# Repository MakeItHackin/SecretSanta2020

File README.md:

# SecretSanta2020
Overview of Reddit Secret Santa gift from 2020

Watch the Demo Here:
https://youtu.be/uKTaNg_Iy-Q

Review the User Guide PDF for details

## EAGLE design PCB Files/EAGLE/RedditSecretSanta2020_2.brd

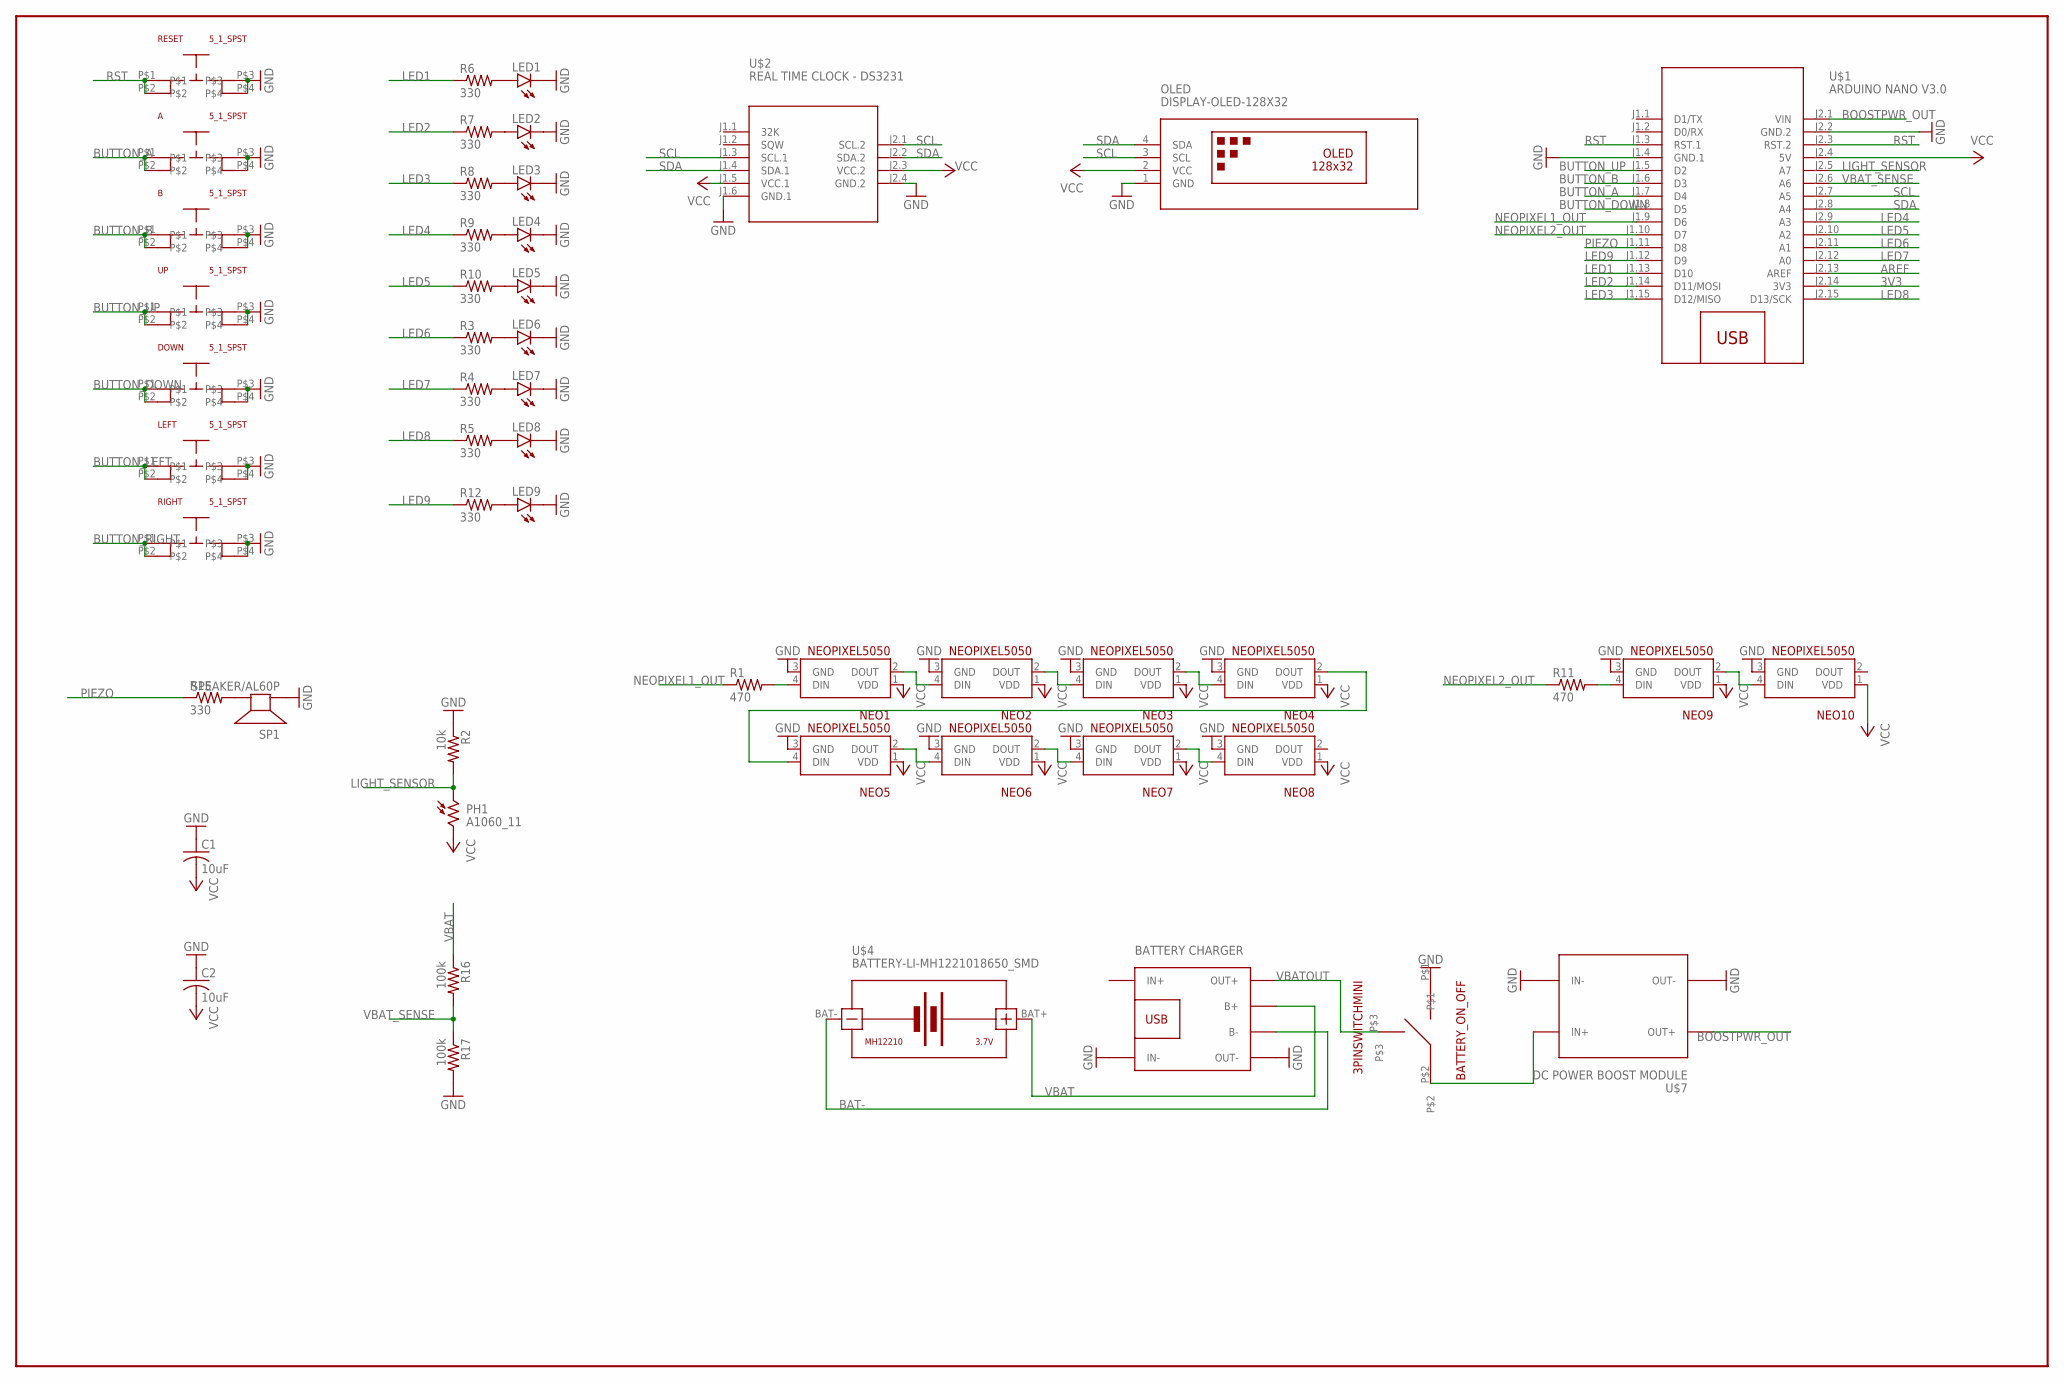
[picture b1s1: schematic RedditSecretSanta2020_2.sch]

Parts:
A: 5_1_SPST
B: 5_1_SPST
BATTERY_ON_OFF: 3PINSWITCHMINI; 3PINMINI
C1, C2: 10uF; C0805
DOWN: 5_1_SPST
LED1, LED2, LED3, LED4, LED5, LED6, LED7, LED8, LED9: LEDSML0805; SML0805
LEFT: 5_1_SPST
NEO1, NEO2, NEO3, NEO4, NEO5, NEO6, NEO7, NEO8, NEO9, NEO10: NEOPIXEL5050
OLED: DISPLAY-OLED-128X32
PH1: A1060_11; T0-46-A10XX
R1, R11: 470; R0805
R2: 10k; R0805
R3, R4, R5, R6, R7, R8, R9, R10, R12, R15: 330; R0805
R16, R17: 100k; R0805
RESET: 5_1_SPST
RIGHT: 5_1_SPST
SP1: SPEAKER/AL60P; AL60P
U$1: ARDUINO NANO V3.0; ARDUINO-NANO-3.0
U$2: REAL TIME CLOCK - DS3231; RTC-DS3231-AT24C32
U$4: BATTERY-LI-MH1221018650_SMD; BATTERY_18650_SMD
U$6: BATTERY CHARGER; BAT_CHARGE_LOW_FP
U$7: DC POWER BOOST MODULE; DC-DC-STEP-UP-LOW_FP
UP: 5_1_SPST

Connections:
3V3: U$1.J2.14 (3V3)
AREF: U$1.J2.13 (AREF)
BAT-: U$4.BAT-, U$6.B-
BOOSTPWR_OUT: U$1.J2.1 (VIN), U$7.OUT+
BUTTON_A: A.P$1, A.P$2, U$1.J1.7 (D4)
BUTTON_B: B.P$1, B.P$2, U$1.J1.6 (D3)
BUTTON_DOWN: DOWN.P$1, DOWN.P$2, U$1.J1.8 (D5)
BUTTON_LEFT: LEFT.P$1, LEFT.P$2
BUTTON_RIGHT: RIGHT.P$1, RIGHT.P$2
BUTTON_UP: U$1.J1.5 (D2), UP.P$1, UP.P$2
GND: A.P$3, A.P$4, B.P$3, B.P$4, BATTERY_ON_OFF.P$1, C1.1, C2.1, DOWN.P$3, DOWN.P$4, LED1.C, LED2.C, LED3.C, LED4.C, LED5.C, LED6.C, LED7.C, LED8.C, LED9.C, LEFT.P$3, LEFT.P$4, NEO1.3 (GND), NEO2.3 (GND), NEO3.3 (GND), NEO4.3 (GND), NEO5.3 (GND), NEO6.3 (GND), NEO7.3 (GND), NEO8.3 (GND), NEO9.3 (GND), NEO10.3 (GND), OLED.1 (GND), R2.1, R17.2, RESET.P$3, RESET.P$4, RIGHT.P$3, RIGHT.P$4, SP1.1 (+), U$1.J1.4 (GND.1), U$1.J2.2 (GND.2), U$2.J1.6 (GND.1), U$2.J2.4 (GND.2), U$6.IN-, U$6.OUT-, U$7.IN-, U$7.OUT-, UP.P$3, UP.P$4
LED1: R6.1, U$1.J1.13 (D10)
LED1W: LED1.A, R6.2
LED1W1: LED6.A, R3.2
LED2: R7.1, U$1.J1.14 (D11/MOSI)
LED2W: LED2.A, R7.2
LED2W1: LED7.A, R4.2
LED3: R8.1, U$1.J1.15 (D12/MISO)
LED3W: LED3.A, R8.2
LED3W1: LED8.A, R5.2
LED3W2: LED9.A, R12.2
LED4: R9.1, U$1.J2.9 (A3)
LED4W: LED4.A, R9.2
LED5: R10.1, U$1.J2.10 (A2)
LED5W: LED5.A, R10.2
LED6: R3.1, U$1.J2.11 (A1)
LED7: R4.1, U$1.J2.12 (A0)
LED8: R5.1, U$1.J2.15 (D13/SCK)
LED9: R12.1, U$1.J1.12 (D9)
LIGHT_SENSOR: PH1.1, R2.2, U$1.J2.5 (A7)
unnamed: NEO9.4 (DIN), R11.2
unnamed: R15.2, SP1.2 (-)
unnamed: NEO4.2 (DOUT), NEO5.4 (DIN)
unnamed: NEO1.4 (DIN), R1.2
unnamed: NEO1.2 (DOUT), NEO2.4 (DIN)
unnamed: NEO2.2 (DOUT), NEO3.4 (DIN)
unnamed: NEO3.2 (DOUT), NEO4.4 (DIN)
unnamed: NEO5.2 (DOUT), NEO6.4 (DIN)
unnamed: NEO6.2 (DOUT), NEO7.4 (DIN)
unnamed: NEO7.2 (DOUT), NEO8.4 (DIN)
unnamed: NEO9.2 (DOUT), NEO10.4 (DIN)
NEOPIXEL1_OUT: R1.1, U$1.J1.9 (D6)
NEOPIXEL2_OUT: R11.1, U$1.J1.10 (D7)
PIEZO: R15.1, U$1.J1.11 (D8)
RST: RESET.P$1, RESET.P$2, U$1.J1.3 (RST.1), U$1.J2.3 (RST.2)
SCL: OLED.3 (SCL), U$1.J2.7 (A5), U$2.J1.3 (SCL.1), U$2.J2.1 (SCL.2)
SDA: OLED.4 (SDA), U$1.J2.8 (A4), U$2.J1.4 (SDA.1), U$2.J2.2 (SDA.2)
VBAT: R16.1, U$4.BAT+, U$6.B+
VBATOUT: BATTERY_ON_OFF.P$3, U$6.OUT+
VBAT_SENSE: R16.2, R17.1, U$1.J2.6 (A6)
VBOOST_IN: BATTERY_ON_OFF.P$2, U$7.IN+
VCC: C1.2, C2.2, NEO1.1 (VDD), NEO2.1 (VDD), NEO3.1 (VDD), NEO4.1 (VDD), NEO5.1 (VDD), NEO6.1 (VDD), NEO7.1 (VDD), NEO8.1 (VDD), NEO9.1 (VDD), NEO10.1 (VDD), OLED.2 (VCC), PH1.2, U$1.J2.4 (5V), U$2.J1.5 (VCC.1), U$2.J2.3 (VCC.2)

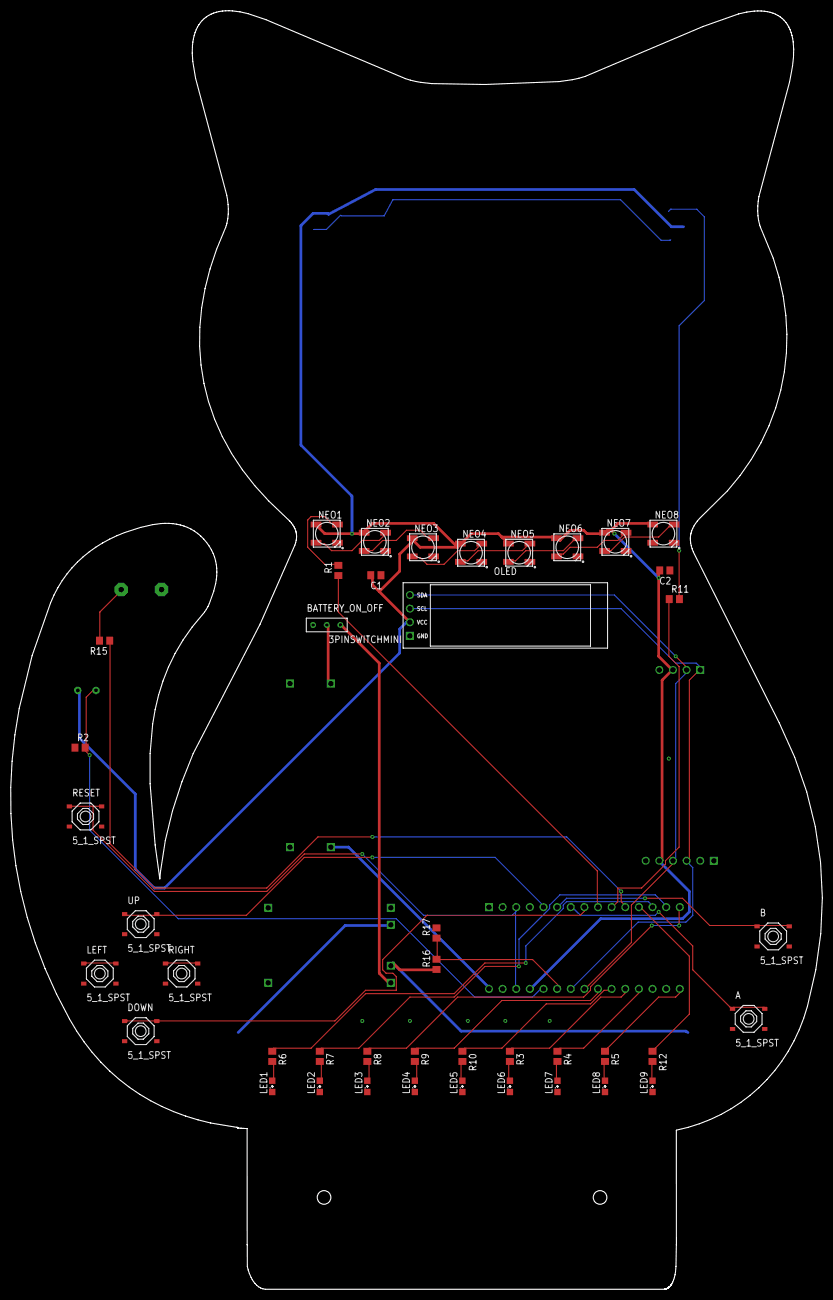
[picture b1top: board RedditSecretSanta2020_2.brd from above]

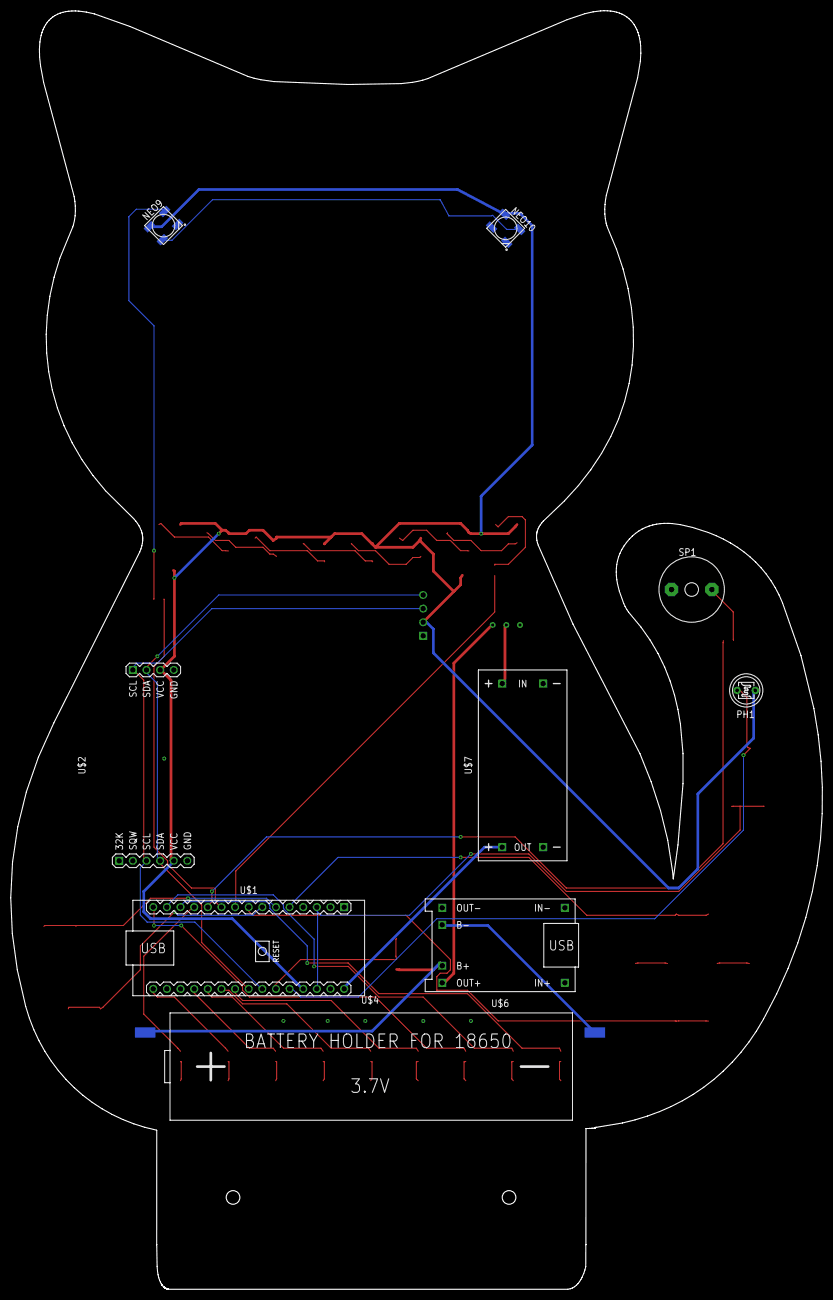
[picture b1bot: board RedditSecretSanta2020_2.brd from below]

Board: 2 copper layers, 151.2 x 238.3 mm, 52 parts (9 on the bottom side), 50 nets.

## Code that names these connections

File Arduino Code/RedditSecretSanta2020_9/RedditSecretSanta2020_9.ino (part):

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// on a live circuit...if you must, connect GND first.

// Assign Input Pins (Buttons and Light sensor)
#define BUTTON_A_PIN 2
#define BUTTON_B_PIN 5
#define BUTTON_C_PIN 3
#define BUTTON_D_PIN 4
#define BATTERY_VOLTAGE_PIN A6
#define LIGHT_SENSOR_PIN A7
#define BUZZER_PIN 8

// LED Pin Assignments
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  colorWipeEyes(stripEyes.Color(0, 0, 0), 0); // Turn Off
  
  //Setup input pins
  pinMode(BUTTON_A_PIN, INPUT_PULLUP);
  pinMode(BUTTON_B_PIN, INPUT_PULLUP);
  pinMode(BUTTON_C_PIN, INPUT_PULLUP);
  pinMode(BUTTON_D_PIN, INPUT_PULLUP);
  pinMode(BATTERY_VOLTAGE_PIN, INPUT);
  pinMode(LIGHT_SENSOR_PIN, INPUT);

  //Setup output pins
  pinMode(BUZZER_PIN,OUTPUT);
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void CheckbuttonA(){

    // Get current button state.
  buttonANewState = digitalRead(BUTTON_A_PIN);

  // Check if state changed from high to low (button press).
  if (buttonANewState == LOW && buttonAOldState == HIGH) {
    // Short delay to debounce button.
    delay(20);
    // Check if button is still low after debounce.
    buttonANewState = digitalRead(BUTTON_A_PIN);
    if (buttonANewState == LOW) {
      // BUTTON PRESSED
     Serial.println("BUTTON A PRESSED");
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void CheckbuttonB(){

    // Get current button state.
  buttonBNewState = digitalRead(BUTTON_B_PIN);

  // Check if state changed from high to low (button press).
  if (buttonBNewState == LOW && buttonBOldState == HIGH) {
    // Short delay to debounce button.
    delay(20);
    // Check if button is still low after debounce.
    buttonBNewState = digitalRead(BUTTON_B_PIN);
    if (buttonBNewState == LOW) {
      // BUTTON PRESSED
     Serial.println("BUTTON B PRESSED");
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  byte collarBrightness = 20;
  
  while (digitalRead(BUTTON_D_PIN) == HIGH) {
        if (digitalRead(BUTTON_B_PIN) == LOW) {
          ////display.setCursor(0,35);
          ////display.print("    ");
        NewCollar++;
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       delay(50);
        }
      }
        if (digitalRead(BUTTON_A_PIN) == LOW) {
          ////display.setCursor(0,35);
          ////display.print("    ");
        NewCollar--;
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  
  while (digitalRead(BUTTON_D_PIN) == HIGH) {
    
        if (digitalRead(BUTTON_B_PIN) == LOW) {
          ////display.setCursor(0,35);
          ////display.print("    ");
        NewSong++;
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        */
      }
      
        if (digitalRead(BUTTON_A_PIN) == LOW) {
          ////display.setCursor(0,35);
          ////display.print("    ");
        NewSong--;
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  byte eyeBrightness = 200;
  
  while (digitalRead(BUTTON_D_PIN) == HIGH) {
        if (digitalRead(BUTTON_B_PIN) == LOW) {
          ////display.setCursor(0,35);
          ////display.print("    ");
        NewEyes++;
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       delay(50);
        }
      }
        if (digitalRead(BUTTON_A_PIN) == LOW) {
          ////display.setCursor(0,35);
          ////display.print("    ");
        NewEyes--;
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  display.setCursor(0,0);
  //display.setTextSize(2);
  display.print("VALUE: ");
  display.print(analogRead(LIGHT_SENSOR_PIN));
  display.println(" ");
  //display.println("             ");
  //display.println("             ");
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    display.println("LIGHT SENSOR VALUE");
    display.setCursor(35,10);
    display.setTextSize(3);
    display.print(analogRead(LIGHT_SENSOR_PIN));
    display.println("      ");
    display.display();
    delay(50);
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  //delay(50);

  while (digitalRead(BUTTON_D_PIN) == HIGH) {
        if (digitalRead(BUTTON_B_PIN) == LOW) {
          ////display.setCursor(0,35);
          ////display.print("    ");
        NewHour++;
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       delay(50);
        }
      }
            if (digitalRead(BUTTON_A_PIN) == LOW) {
          ////display.setCursor(0,35);
          ////display.print("    ");
        NewHour--;
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delay(500);

  while (digitalRead(BUTTON_D_PIN) == HIGH) {
        if (digitalRead(BUTTON_B_PIN) == LOW) {
          //display.setCursor(0,35);
          //display.print("    ");
        NewMinute++;
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       delay(50);
        }
      }
        if (digitalRead(BUTTON_A_PIN) == LOW) {
          //display.setCursor(0,35);
          //display.print("    ");
        NewMinute--;
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delay(500);

  while (digitalRead(BUTTON_D_PIN) == HIGH) {
        if (digitalRead(BUTTON_B_PIN) == LOW) {
         //// display.setCursor(0,35);
        ////  display.print("    ");
        NewSecond++;
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       delay(50);
        }
      }
        if (digitalRead(BUTTON_A_PIN) == LOW) {
         //// display.setCursor(0,35);
        ////  display.print("    ");
        NewSecond--;
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}

  while (digitalRead(BUTTON_D_PIN) == HIGH) {
        if (digitalRead(BUTTON_B_PIN) == LOW) {
          //display.setCursor(0,35);
          //display.print("    ");
        NewYear++;
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       delay(50);
        }
      }
        if (digitalRead(BUTTON_A_PIN) == LOW) {
          //display.setCursor(0,35);
          //display.print("    ");
        NewYear--;
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delay(500);

  while (digitalRead(BUTTON_D_PIN) == HIGH) {
        if (digitalRead(BUTTON_B_PIN) == LOW) {
         // display.setCursor(0,35);
         // display.print("    ");
        NewMonth++;
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       delay(50);
        }
      }
        if (digitalRead(BUTTON_A_PIN) == LOW) {
         // display.setCursor(0,35);
         // display.print("    ");
        NewMonth--;
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delay(500);

  while (digitalRead(BUTTON_D_PIN) == HIGH) {
        if (digitalRead(BUTTON_B_PIN) == LOW) {
          //display.setCursor(0,35);
          //display.print("    ");
        NewDate++;
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        }

      }
if (digitalRead(BUTTON_A_PIN) == LOW) {
          //display.setCursor(0,35);
          //display.print("    ");
        NewDate--;
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  }
  if (LightSensorMenuSelected == 1){
    for (int i = 0; i < 100; i++)  {
////       printLEDNumber(analogRead(LIGHT_SENSOR_PIN)); 
       delay(150);     
    }
////    quadDisplayString("----");   
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
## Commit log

2020-12-21 Create Arduino Code

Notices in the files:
PCB Files/EAGLE/RedditSecretSanta2020_2.brd:
TRADEMARKS AND COPYRIGHT USED WITH ARTISTIC LICENSE.  NOT FOR SALE
parts and their libraries:
diy-modules: Released under the Creative Commons Attribution 4.0 International License: http://creativecommons.org/licenses/by/4.0
